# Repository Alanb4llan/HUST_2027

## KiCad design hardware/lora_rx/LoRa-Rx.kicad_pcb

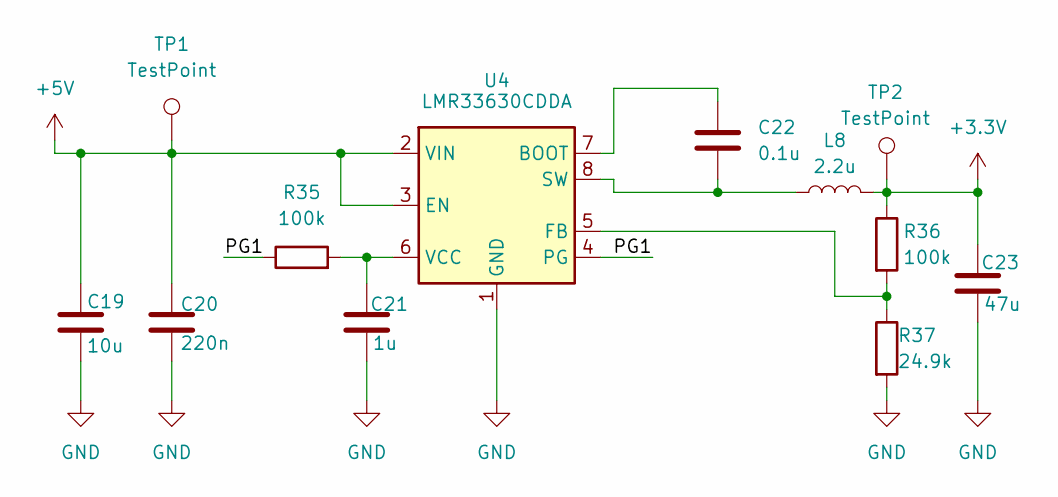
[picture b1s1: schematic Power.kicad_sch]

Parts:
C19: 10u; C_Elec_6.3x5.4
C20: 220n; C_0402_1005Metric_Pad0.74x0.62mm_HandSolder
C21: 1u; C_0402_1005Metric_Pad0.74x0.62mm_HandSolder
C22: 0.1u; C_0402_1005Metric_Pad0.74x0.62mm_HandSolder
C23: 47u; C_Elec_6.3x5.4
L8: 2.2u; L_7.3x7.3_H4.5
R35, R36: 100k; R_0402_1005Metric_Pad0.72x0.64mm_HandSolder
R37: 24.9k; R_0402_1005Metric_Pad0.72x0.64mm_HandSolder
TP1, TP2: TestPoint; TestPoint_THTPad_D1.0mm_Drill0.5mm
U4: LMR33630CDDA; Texas_HSOP-8-1EP_3.9x4.9mm_P1.27mm_ThermalVias

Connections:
+3.3V: C23.1, L8.2, R36.1, TP2.1 (1_1); also elsewhere on the board
+5V: C19.1, C20.1, TP1.1 (1_1), U4.2 (VIN), U4.3 (EN); also elsewhere on the board
/Power/PG1: R35.1, U4.4 (PG)
GND: C19.2, C20.2, C21.2, C23.2, R37.2, U4.1 (GND), U4.9 (GND); also elsewhere on the board
unnamed: C22.1, U4.7 (BOOT)
unnamed: R36.2, R37.1, U4.5 (FB)
unnamed: C22.2, L8.1, U4.8 (SW)
unnamed: C21.1, R35.2, U4.6 (VCC)

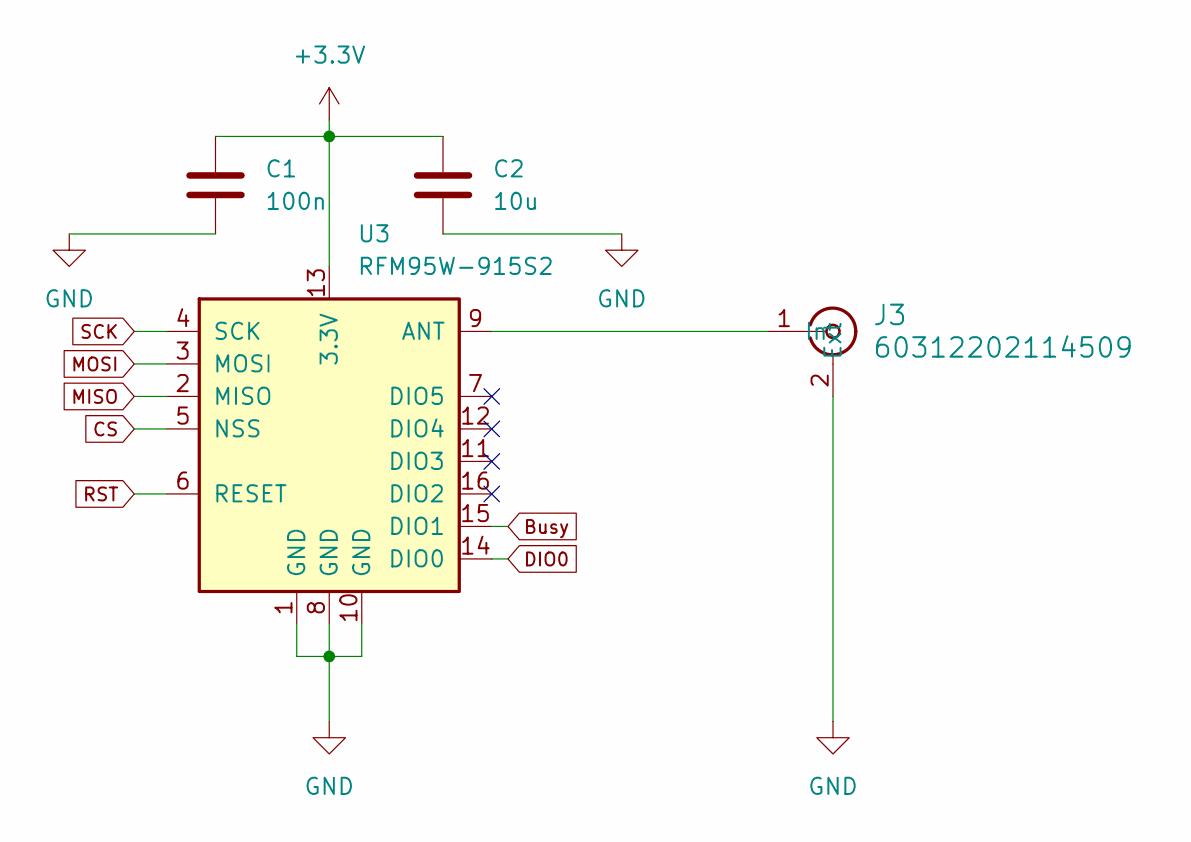
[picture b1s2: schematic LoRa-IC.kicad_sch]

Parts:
C1: 100n; C_0402_1005Metric_Pad0.74x0.62mm_HandSolder
C2: 10u; C_0603_1608Metric_Pad1.08x0.95mm_HandSolder
J3: 60312202114509; CONN_60312202114509_WRE
U3: RFM95W-915S2; HOPERF_RFM9XW_SMD

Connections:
+3.3V: C1.1, C2.1, U3.13 (3.3V); also elsewhere on the board
Busy: U3.15 (DIO1); also elsewhere on the board
CS: U3.5 (NSS); also elsewhere on the board
DIO0: U3.14 (DIO0); also elsewhere on the board
GND: C1.2, C2.2, J3.2 (Ext), J3.3 (Ext), J3.4 (Ext), J3.5 (Ext), U3.1 (GND), U3.8 (GND), U3.10 (GND); also elsewhere on the board
MISO: U3.2 (MISO); also elsewhere on the board
MOSI: U3.3 (MOSI); also elsewhere on the board
unnamed: J3.1 (In), U3.9 (ANT)
RST: U3.6 (RESET); also elsewhere on the board
SCK: U3.4 (SCK); also elsewhere on the board

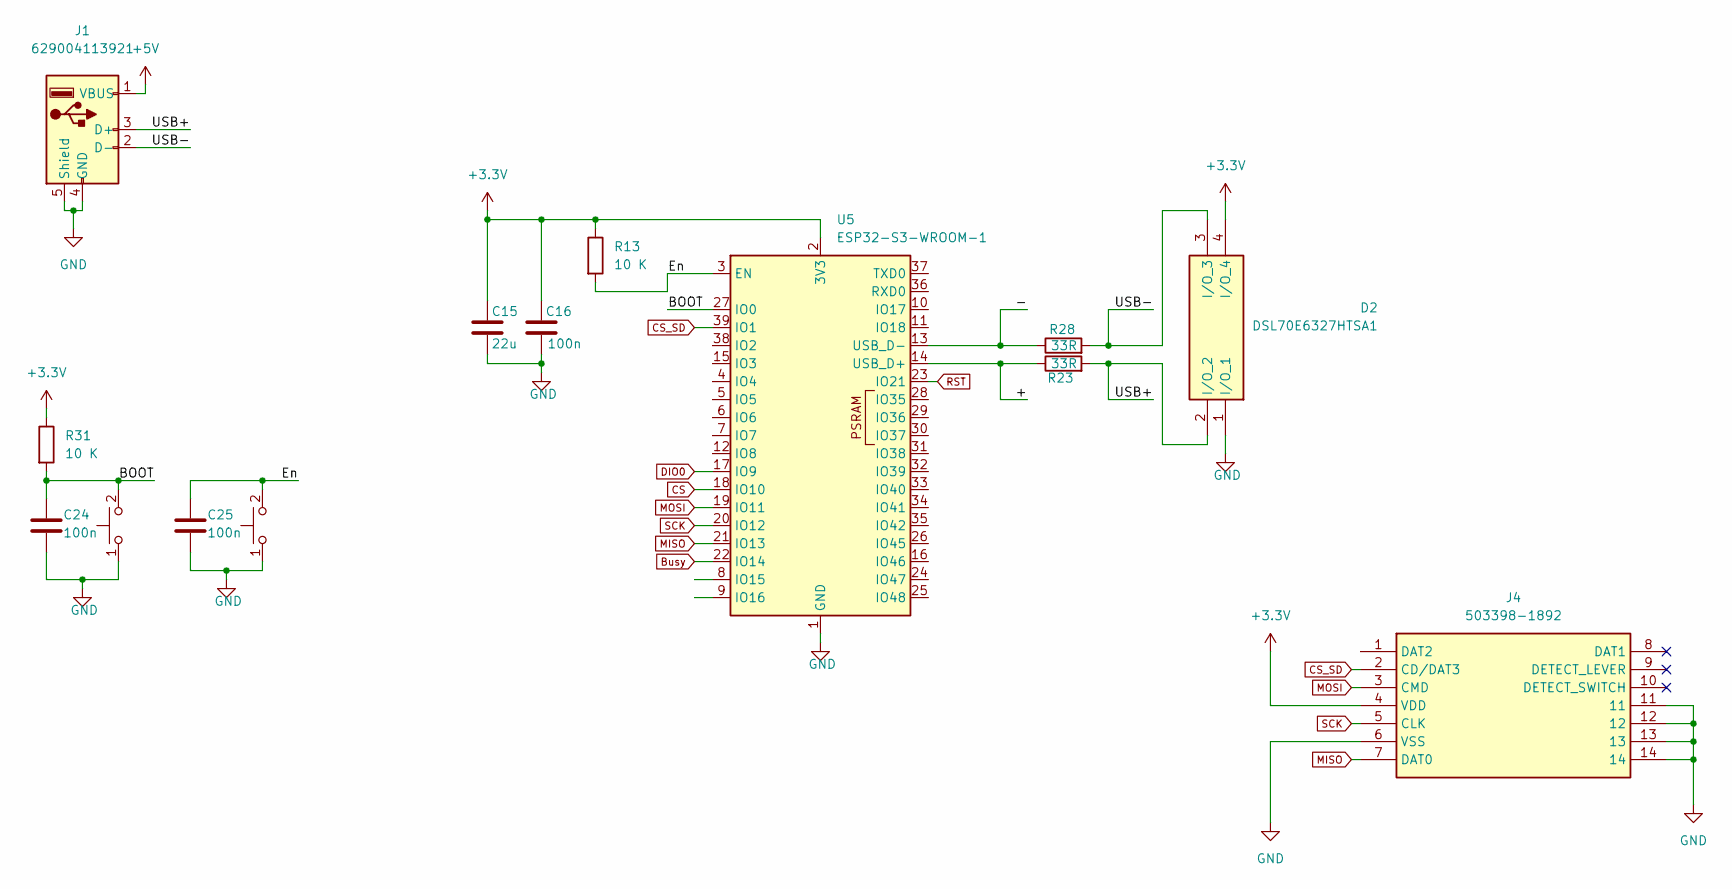
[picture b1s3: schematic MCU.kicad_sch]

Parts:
C15: 22u; C_1206_3216Metric_Pad1.33x1.80mm_HandSolder
C16, C24, C25: 100n; C_0402_1005Metric_Pad0.74x0.62mm_HandSolder
D2: DSL70E6327HTSA1; Mouser Part Number 726-DSL70E6327HTSA1
IC1, IC2: TS04-66-65-BK-260-SMT; TS046665BK260SMT; Mouser Part Number 179-TS046665BK260SMT
J1: 629004113921; Mouser Part Number 710-629004113921
J4: 503398-1892; 5033981892; Mouser Part Number 538-503398-1892
R13, R31: 10 K; R_0402_1005Metric_Pad0.72x0.64mm_HandSolder
R23, R28: 33R; R_0402_1005Metric_Pad0.72x0.64mm_HandSolder
U5: ESP32-S3-WROOM-1; ESP32-S3-WROOM-1U

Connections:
+3.3V: C15.1, C16.1, D2.4 (I/O_4), J4.4 (VDD), R13.1, R31.1, U5.2 (3V3); also elsewhere on the board
+5V: J1.1 (VBUS); also elsewhere on the board
/MCU/+: R23.1, U5.14 (USB_D+)
/MCU/-: R28.1, U5.13 (USB_D-)
/MCU/BOOT: C24.1, IC1.2, IC1.4, R31.2, U5.27 (IO0)
/MCU/En: C25.1, IC2.2, IC2.4, R13.2, U5.3 (EN)
/MCU/USB+: D2.2 (I/O_2), J1.3 (D+), R23.2
/MCU/USB-: D2.3 (I/O_3), J1.2 (D-), R28.2
Busy: U5.22 (IO14); also elsewhere on the board
CS: U5.18 (IO10); also elsewhere on the board
CS_SD: J4.2 (CD/DAT3), U5.39 (IO1)
DIO0: U5.17 (IO9); also elsewhere on the board
GND: C15.2, C16.2, C24.2, C25.2, D2.1 (I/O_1), IC1.1, IC1.3, IC2.1, IC2.3, J1.4 (GND), J1.5 (Shield), J1.6 (Shield), J4.6 (VSS), J4.11, J4.12, J4.13, J4.14, U5.1 (GND), U5.40 (GND), U5.41 (GND); also elsewhere on the board
MISO: J4.7 (DAT0), U5.21 (IO13); also elsewhere on the board
MOSI: J4.3 (CMD), U5.19 (IO11); also elsewhere on the board
RST: U5.23 (IO21); also elsewhere on the board
SCK: J4.5 (CLK), U5.20 (IO12); also elsewhere on the board

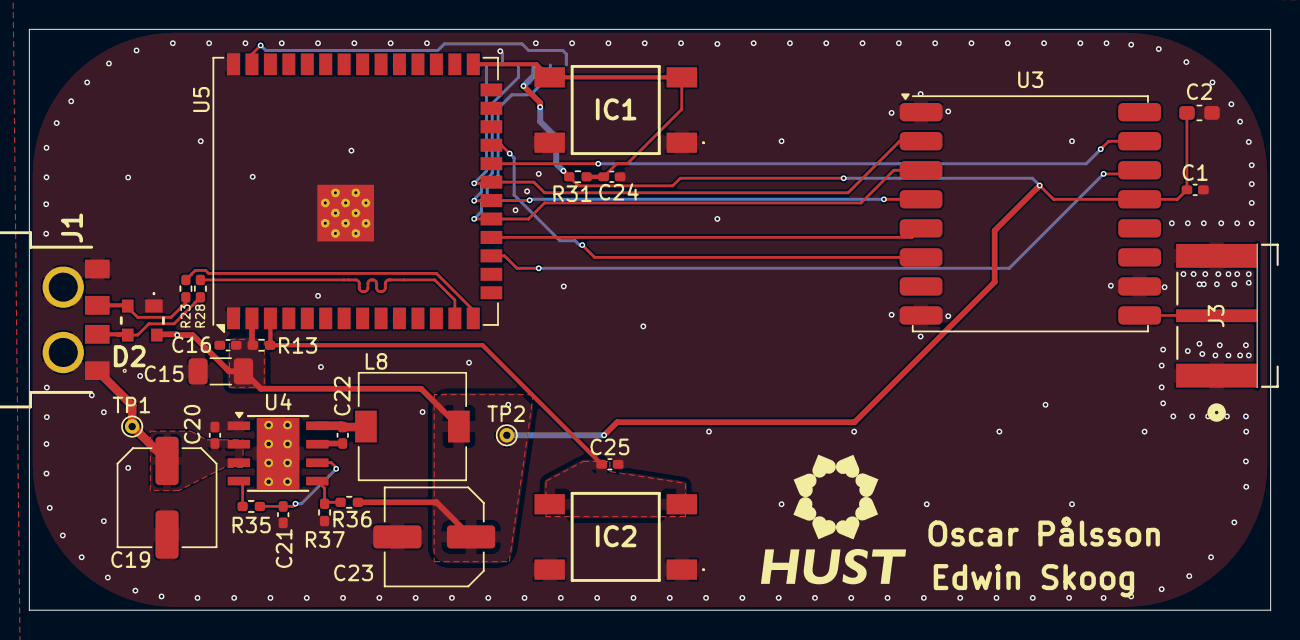
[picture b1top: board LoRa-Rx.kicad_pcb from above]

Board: 2 copper layers, 85.5 x 40.0 mm, 30 parts (1 on the bottom side), 23 nets.

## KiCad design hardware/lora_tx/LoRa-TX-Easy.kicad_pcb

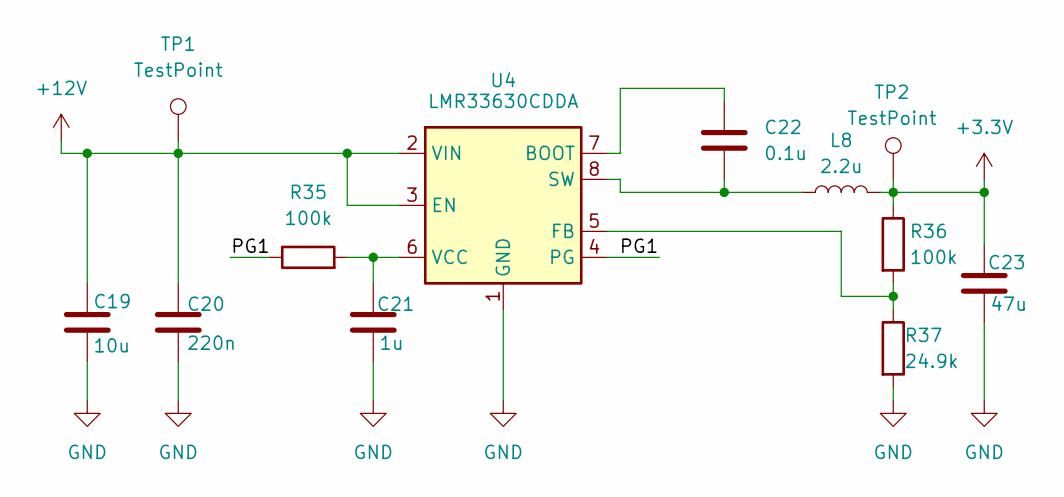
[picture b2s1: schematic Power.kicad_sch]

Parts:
C19: 10u; C_Elec_6.3x5.4
C20: 220n; C_0402_1005Metric_Pad0.74x0.62mm_HandSolder
C21: 1u; C_0402_1005Metric_Pad0.74x0.62mm_HandSolder
C22: 0.1u; C_0402_1005Metric_Pad0.74x0.62mm_HandSolder
C23: 47u; C_Elec_6.3x5.4
L8: 2.2u; L_7.3x7.3_H4.5
R35, R36: 100k; R_0402_1005Metric_Pad0.72x0.64mm_HandSolder
R37: 24.9k; R_0402_1005Metric_Pad0.72x0.64mm_HandSolder
TP1, TP2: TestPoint; TestPoint_THTPad_D1.0mm_Drill0.5mm
U4: LMR33630CDDA; Texas_HSOP-8-1EP_3.9x4.9mm_P1.27mm_ThermalVias

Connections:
+3.3V: C23.1, L8.2, R36.1, TP2.1 (1_1); also elsewhere on the board
+12V: C19.1, C20.1, TP1.1 (1_1), U4.2 (VIN), U4.3 (EN); also elsewhere on the board
/Power/PG1: R35.1, U4.4 (PG)
GND: C19.2, C20.2, C21.2, C23.2, R37.2, U4.1 (GND), U4.9 (GND); also elsewhere on the board
unnamed: C22.1, U4.7 (BOOT)
unnamed: R36.2, R37.1, U4.5 (FB)
unnamed: C22.2, L8.1, U4.8 (SW)
unnamed: C21.1, R35.2, U4.6 (VCC)

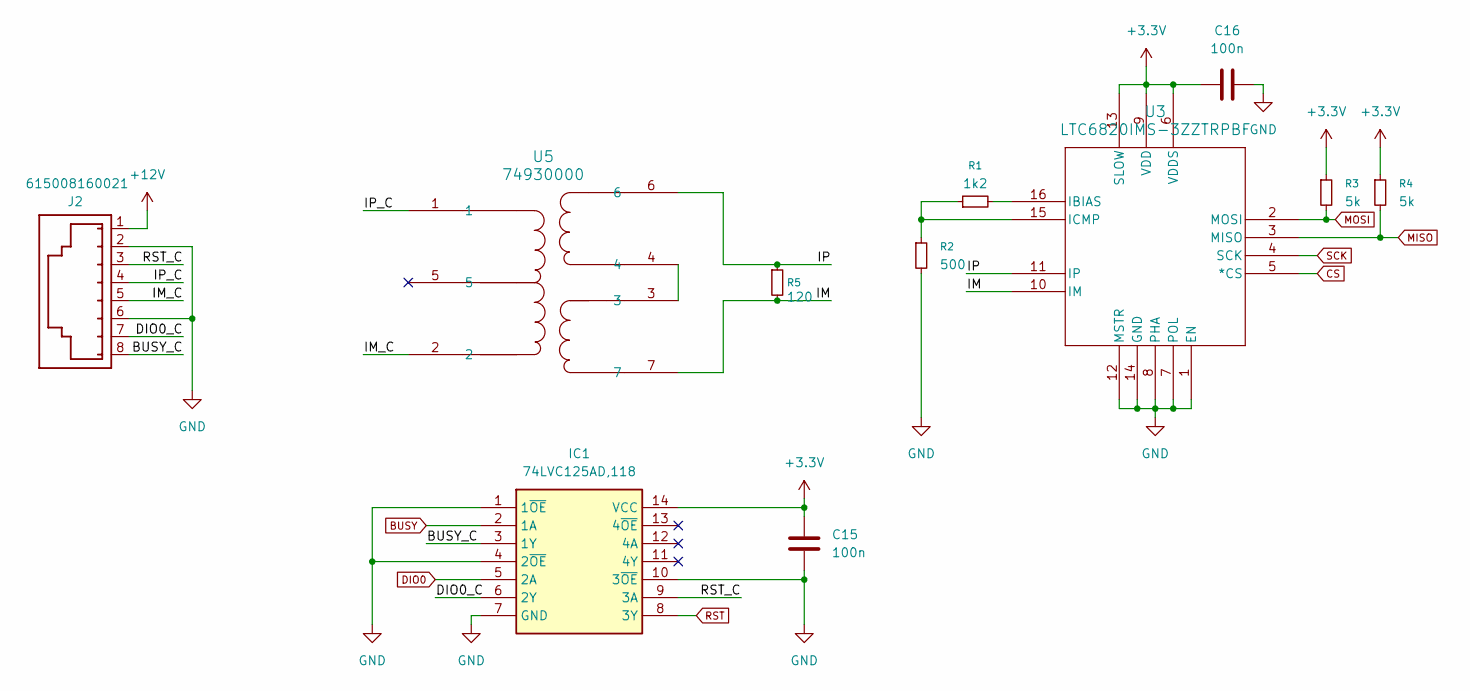
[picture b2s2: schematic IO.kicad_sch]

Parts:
C15, C16: 100n; C_0402_1005Metric_Pad0.74x0.62mm_HandSolder
IC1: 74LVC125AD,118; 74LVC125AD118; Mouser Part Number 771-74LVC125AD-T
J2: 615008160021; J_Wurth_WR-MJ_615008160021
R1: 1k2; R_0402_1005Metric_Pad0.72x0.64mm_HandSolder
R2: 500; R_0402_1005Metric_Pad0.72x0.64mm_HandSolder
R3, R4: 5k; R_0402_1005Metric_Pad0.72x0.64mm_HandSolder
R5: 120; R_0402_1005Metric_Pad0.72x0.64mm_HandSolder
U3: LTC6820IMS-3ZZTRPBF; MS_05-08-1669_ADI
U5: 74930000; SON_930000_WRE

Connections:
+3.3V: C15.1, C16.1, IC1.14 (VCC), R3.1, R4.1, U3.6 (VDDS), U3.9 (VDD), U3.13 (SLOW); also elsewhere on the board
+12V: J2.1; also elsewhere on the board
/IO/BUSY_C: IC1.3 (1Y), J2.8
/IO/DIO0_C: IC1.6 (2Y), J2.7
/IO/IM: R5.2, U3.10 (IM), U5.7
/IO/IM_C: J2.5, U5.2
/IO/IP: R5.1, U3.11 (IP), U5.6
/IO/IP_C: J2.4, U5.1
/IO/RST_C: IC1.9 (3A), J2.3
BUSY: IC1.2 (1A); also elsewhere on the board
CS: U3.5 (*CS); also elsewhere on the board
DIO0: IC1.5 (2A); also elsewhere on the board
GND: C15.2, C16.2, IC1.1 (1~OE), IC1.4 (2~OE), IC1.7 (GND), IC1.10 (3~OE), J2.2, J2.6, R2.2, U3.1 (EN), U3.7 (POL), U3.8 (PHA), U3.12 (MSTR), U3.14 (GND); also elsewhere on the board
MISO: R4.2, U3.3 (MISO); also elsewhere on the board
MOSI: R3.2, U3.2 (MOSI); also elsewhere on the board
unnamed: R1.2, U3.16 (IBIAS)
unnamed: R1.1, R2.1, U3.15 (ICMP)
unnamed: U5.3, U5.4
RST: IC1.8 (3Y); also elsewhere on the board
SCK: U3.4 (SCK); also elsewhere on the board

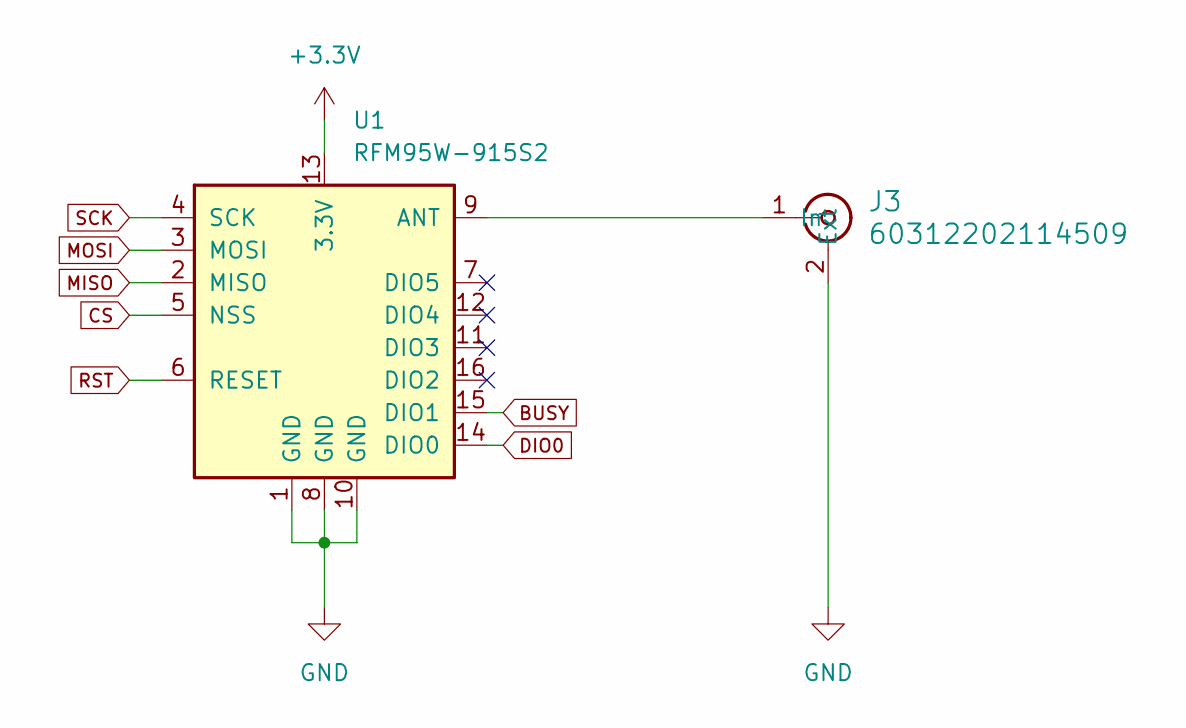
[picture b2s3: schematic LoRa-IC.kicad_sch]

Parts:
J3: 60312202114509; CONN_60312202114509_WRE
U1: RFM95W-915S2; HOPERF_RFM9XW_SMD

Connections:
+3.3V: U1.13 (3.3V); also elsewhere on the board
BUSY: U1.15 (DIO1); also elsewhere on the board
CS: U1.5 (NSS); also elsewhere on the board
DIO0: U1.14 (DIO0); also elsewhere on the board
GND: J3.2 (Ext), J3.3 (Ext), J3.4 (Ext), J3.5 (Ext), U1.1 (GND), U1.8 (GND), U1.10 (GND); also elsewhere on the board
MISO: U1.2 (MISO); also elsewhere on the board
MOSI: U1.3 (MOSI); also elsewhere on the board
unnamed: J3.1 (In), U1.9 (ANT)
RST: U1.6 (RESET); also elsewhere on the board
SCK: U1.4 (SCK); also elsewhere on the board

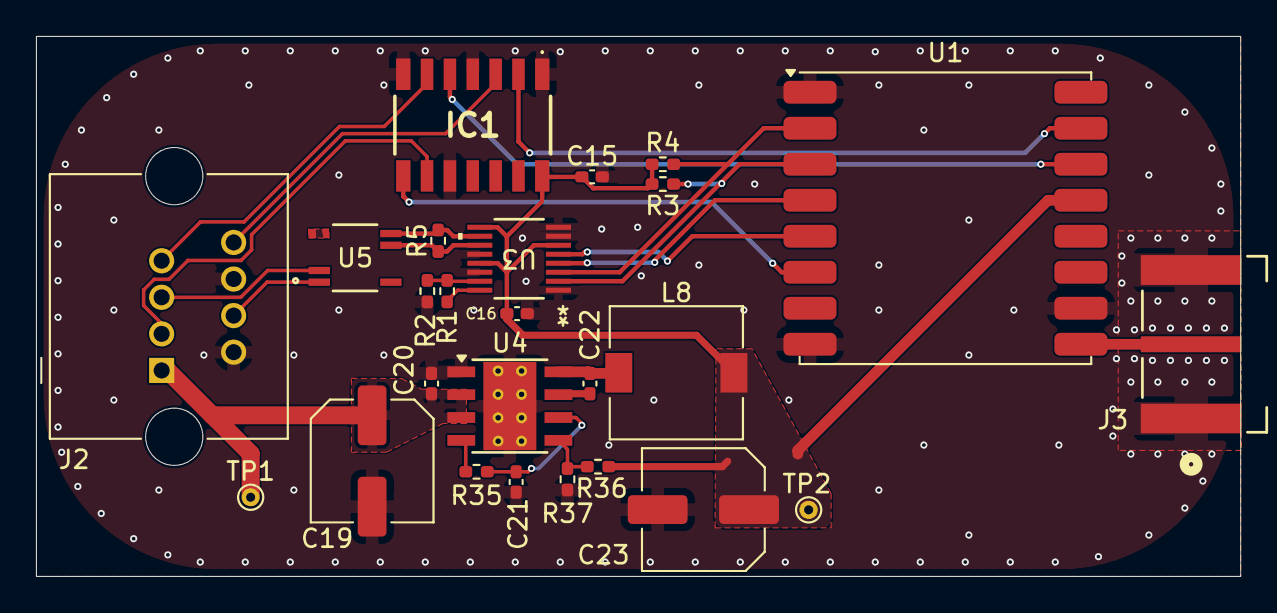
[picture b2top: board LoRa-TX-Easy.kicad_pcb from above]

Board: 2 copper layers, 66.9 x 30.0 mm, 25 parts (0 on the bottom side), 26 nets.

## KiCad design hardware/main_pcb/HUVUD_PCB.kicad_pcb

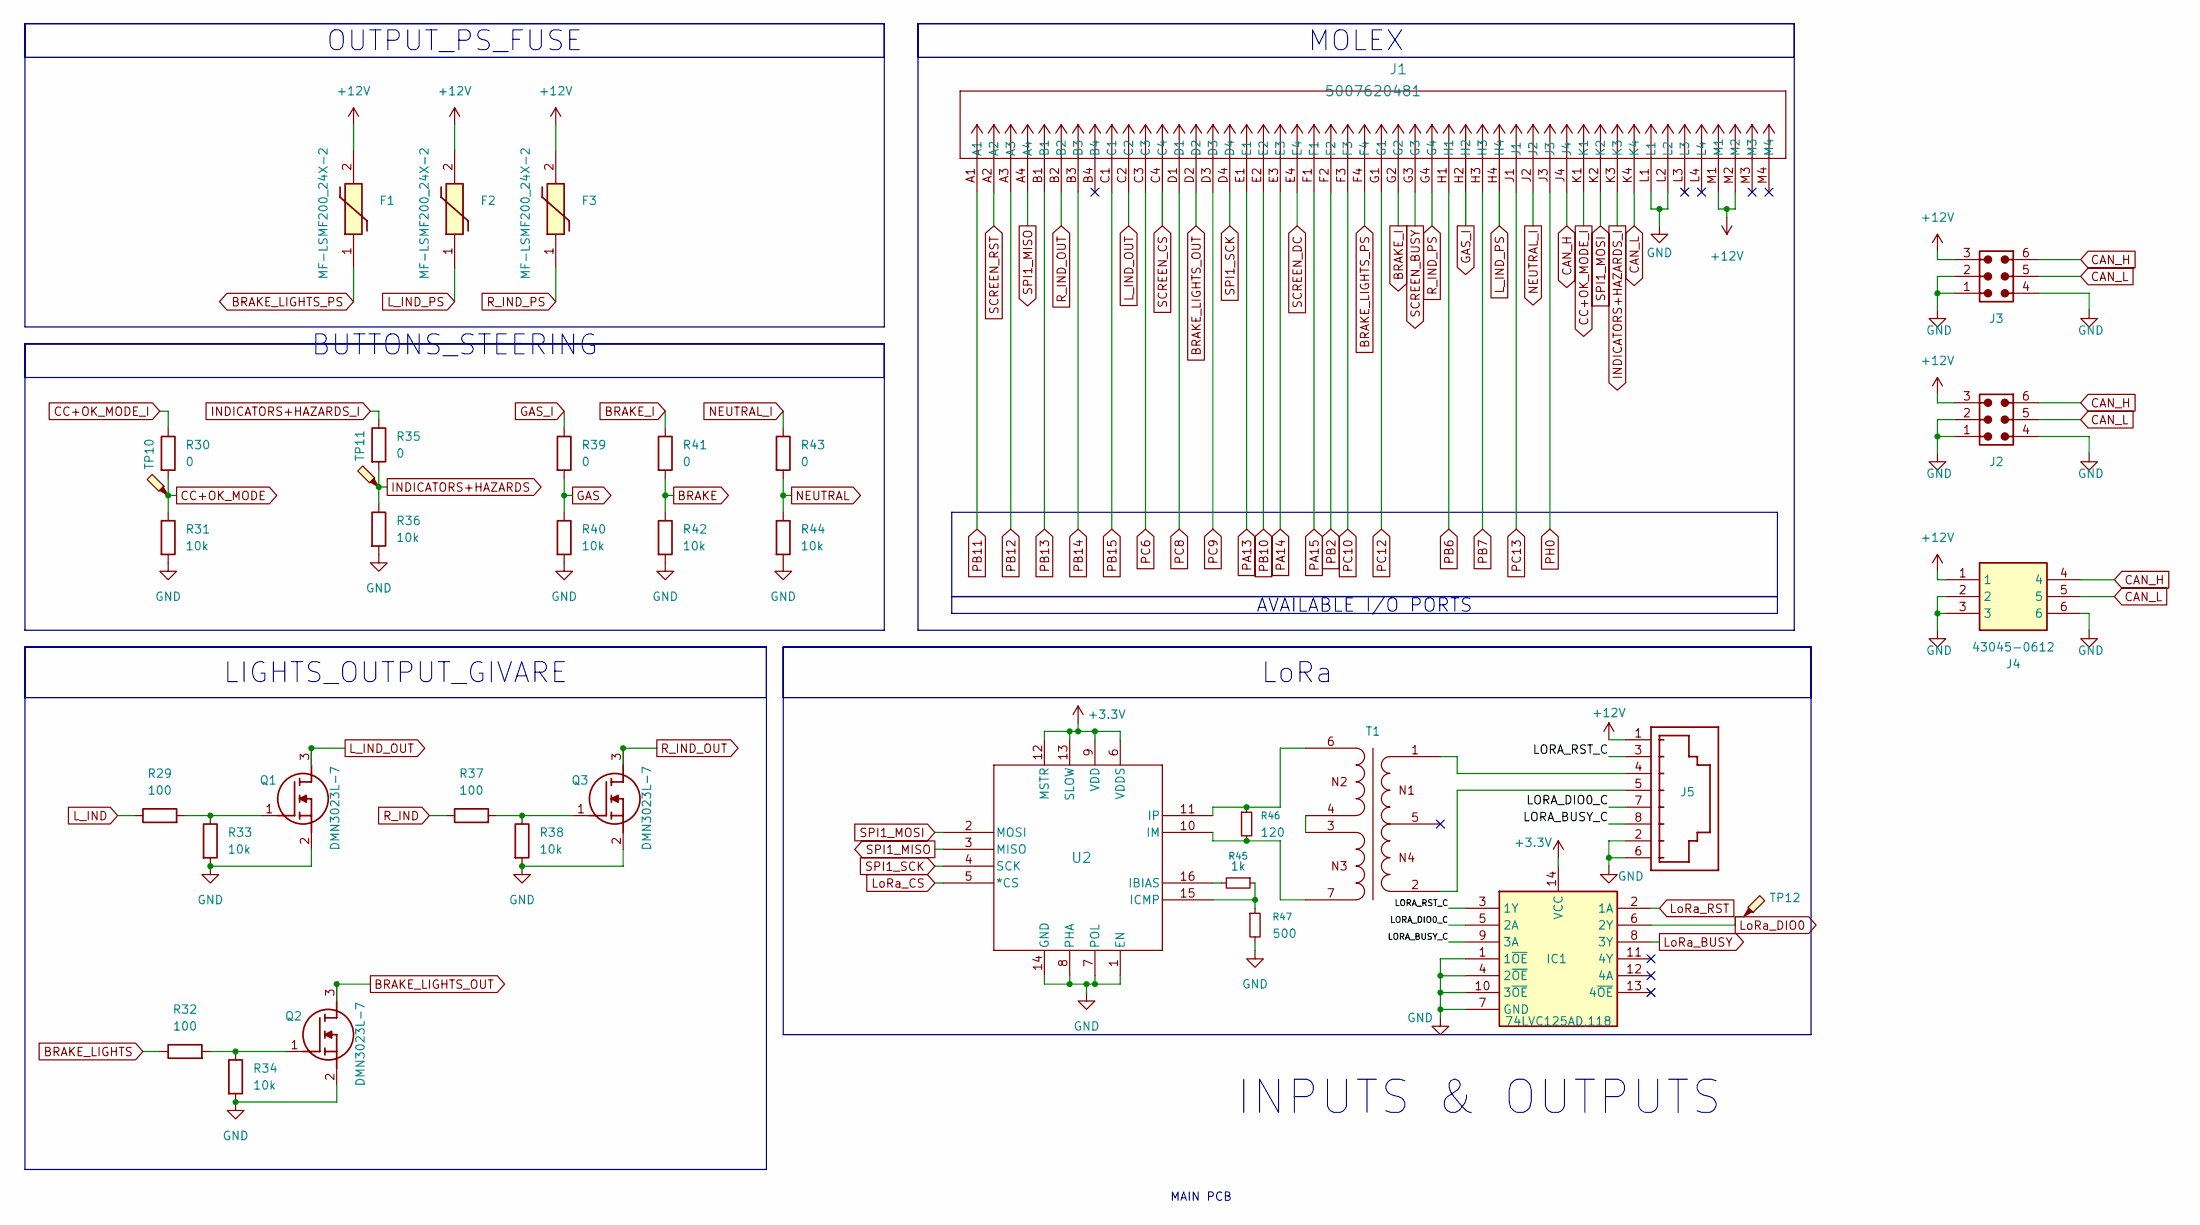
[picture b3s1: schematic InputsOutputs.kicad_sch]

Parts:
F1, F2, F3: MF-LSMF200_24X-2; FUSC7451X160N; Mouser Part Number 652-MF-LSMF200/24X-2
IC1: 74LVC125AD,118; 74LVC125AD118; Mouser Part Number 771-74LVC125AD-T
J1: 5007620481; CONN_SD-500762-001_MOL
J2, J3: 66200621122; J_Wurth_WR-MPC3_66200621122; Working Voltage (V (AC)) 250
J4: 43045-0612; 43045-06YY_121314; Mouser Part Number 538-43045-0612
J5: 615008160021
Q1, Q2, Q3: DMN3023L-7; SOT96P240X110-3N; Mouser Part Number 621-DMN3023L-7
R29, R32, R37: 100; R_Wurth_WRIS-RSKS-0603_W
R30, R35, R39, R41, R43: 0; R_Wurth_WRIS-RSKS-0603_W
R31, R33, R34, R36, R38, R40, R42, R44: 10k; R_Wurth_WRIS-RSKS-0603_W
R45: 1k; R_Wurth_WRIS-RSKS-0603_W
R46: 120; R_Wurth_WRIS-RSKS-0603_W
R47: 500; R_Wurth_WRIS-RSKS-0603_W
T1: 4532_74930000; T_Wurth_WE-STST-4532_74930000; Part Number 74930000
TP10, TP11, TP12: TestPoint_Probe; TestPoint_THTPad_2.0x2.0mm_Drill1.0mm
U2: LTC6820IMS-3ZZTRPBF; MS_05-08-1669_ADI-M

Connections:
+3.3V: IC1.14 (VCC), U2.6 (VDDS), U2.9 (VDD), U2.12 (MSTR), U2.13 (SLOW); also elsewhere on the board
+12V: F1.2, F2.2, F3.2, J1.M1, J1.M2, J2.3, J3.3, J4.1, J5.1; also elsewhere on the board
/Outputs/LORA_BUSY_C: IC1.9 (3A), J5.8
/Outputs/LORA_DIO0_C: IC1.5 (2A), J5.7
/Outputs/LORA_RST_C: IC1.3 (1Y), J5.3
BRAKE: R41.2, R42.1; also elsewhere on the board
BRAKE_I: J1.G2, R41.1
BRAKE_LIGHTS: R32.1; also elsewhere on the board
BRAKE_LIGHTS_OUT: J1.D2, Q2.3 (D)
BRAKE_LIGHTS_PS: F1.1, J1.F4
CAN_H: J1.J4, J2.6, J3.6, J4.4; also elsewhere on the board
CAN_L: J1.K4, J2.5, J3.5, J4.5; also elsewhere on the board
CC+OK_MODE: R30.2, R31.1, TP10.1; also elsewhere on the board
CC+OK_MODE_I: J1.K1, R30.1
GAS: R39.2, R40.1; also elsewhere on the board
GAS_I: J1.H2, R39.1
GND: IC1.1 (1~OE), IC1.4 (2~OE), IC1.7 (GND), IC1.10 (3~OE), J1.L1, J1.L2, J2.1, J2.2, J2.4, J3.1, J3.2, J3.4, J4.2, J4.3, J4.6, J5.2, J5.6, Q1.2 (S), Q2.2 (S), Q3.2 (S), R31.2, R33.2, R34.2, R36.2, R38.2, R40.2, R42.2, R44.2, R47.2, U2.1 (EN), U2.7 (POL), U2.8 (PHA), U2.14 (GND); also elsewhere on the board
INDICATORS+HAZARDS: R35.2, R36.1, TP11.1; also elsewhere on the board
INDICATORS+HAZARDS_I: J1.K3, R35.1
L_IND: R29.1; also elsewhere on the board
L_IND_OUT: J1.C2, Q1.3 (D)
L_IND_PS: F2.1, J1.H4
LoRa_BUSY: IC1.8 (3Y); also elsewhere on the board
LoRa_CS: U2.5 (*CS); also elsewhere on the board
LoRa_DIO0: IC1.6 (2Y), TP12.1; also elsewhere on the board
LoRa_RST: IC1.2 (1A); also elsewhere on the board
NEUTRAL: R43.2, R44.1; also elsewhere on the board
NEUTRAL_I: J1.J2, R43.1
unnamed: J5.4, T1.1
unnamed: J5.5, T1.2
unnamed: Q1.1 (G), R29.2, R33.1
unnamed: Q2.1 (G), R32.2, R34.1
unnamed: Q3.1 (G), R37.2, R38.1
unnamed: T1.3, T1.4
unnamed: R45.2, U2.16 (IBIAS)
unnamed: R45.1, R47.1, U2.15 (ICMP)
unnamed: R46.2, T1.7, U2.10 (IM)
unnamed: R46.1, T1.6, U2.11 (IP)
PA13: J1.E1; also elsewhere on the board
PA14: J1.E3; also elsewhere on the board
PA15: J1.F1; also elsewhere on the board
PB2: J1.F2; also elsewhere on the board
PB6: J1.H1; also elsewhere on the board
PB7: J1.H3; also elsewhere on the board
PB10: J1.E2; also elsewhere on the board
PB11: J1.A1; also elsewhere on the board
PB12: J1.A3; also elsewhere on the board
PB13: J1.B1; also elsewhere on the board
PB14: J1.B3; also elsewhere on the board
PB15: J1.C1; also elsewhere on the board
PC6: J1.C3
PC8: J1.D1; also elsewhere on the board
PC9: J1.D3; also elsewhere on the board
PC10: J1.F3; also elsewhere on the board
PC12: J1.G1; also elsewhere on the board
PC13: J1.J1; also elsewhere on the board
PH0: J1.J3; also elsewhere on the board
R_IND: R37.1; also elsewhere on the board
R_IND_OUT: J1.B2, Q3.3 (D)
R_IND_PS: F3.1, J1.G4
SCREEN_BUSY: J1.G3; also elsewhere on the board
SCREEN_CS: J1.C4; also elsewhere on the board
SCREEN_DC: J1.E4; also elsewhere on the board
SCREEN_RST: J1.A2; also elsewhere on the board
SPI1_MISO: J1.A4, U2.3 (MISO); also elsewhere on the board
SPI1_MOSI: J1.K2, U2.2 (MOSI); also elsewhere on the board
SPI1_SCK: J1.D4, U2.4 (SCK); also elsewhere on the board

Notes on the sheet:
MAIN PCB
INPUTS & OUTPUTS
AVAILABLE I/O PORTS
OUTPUT_PS_FUSE
LIGHTS_OUTPUT_GIVARE
LoRa
MOLEX
BUTTONS_STEERING

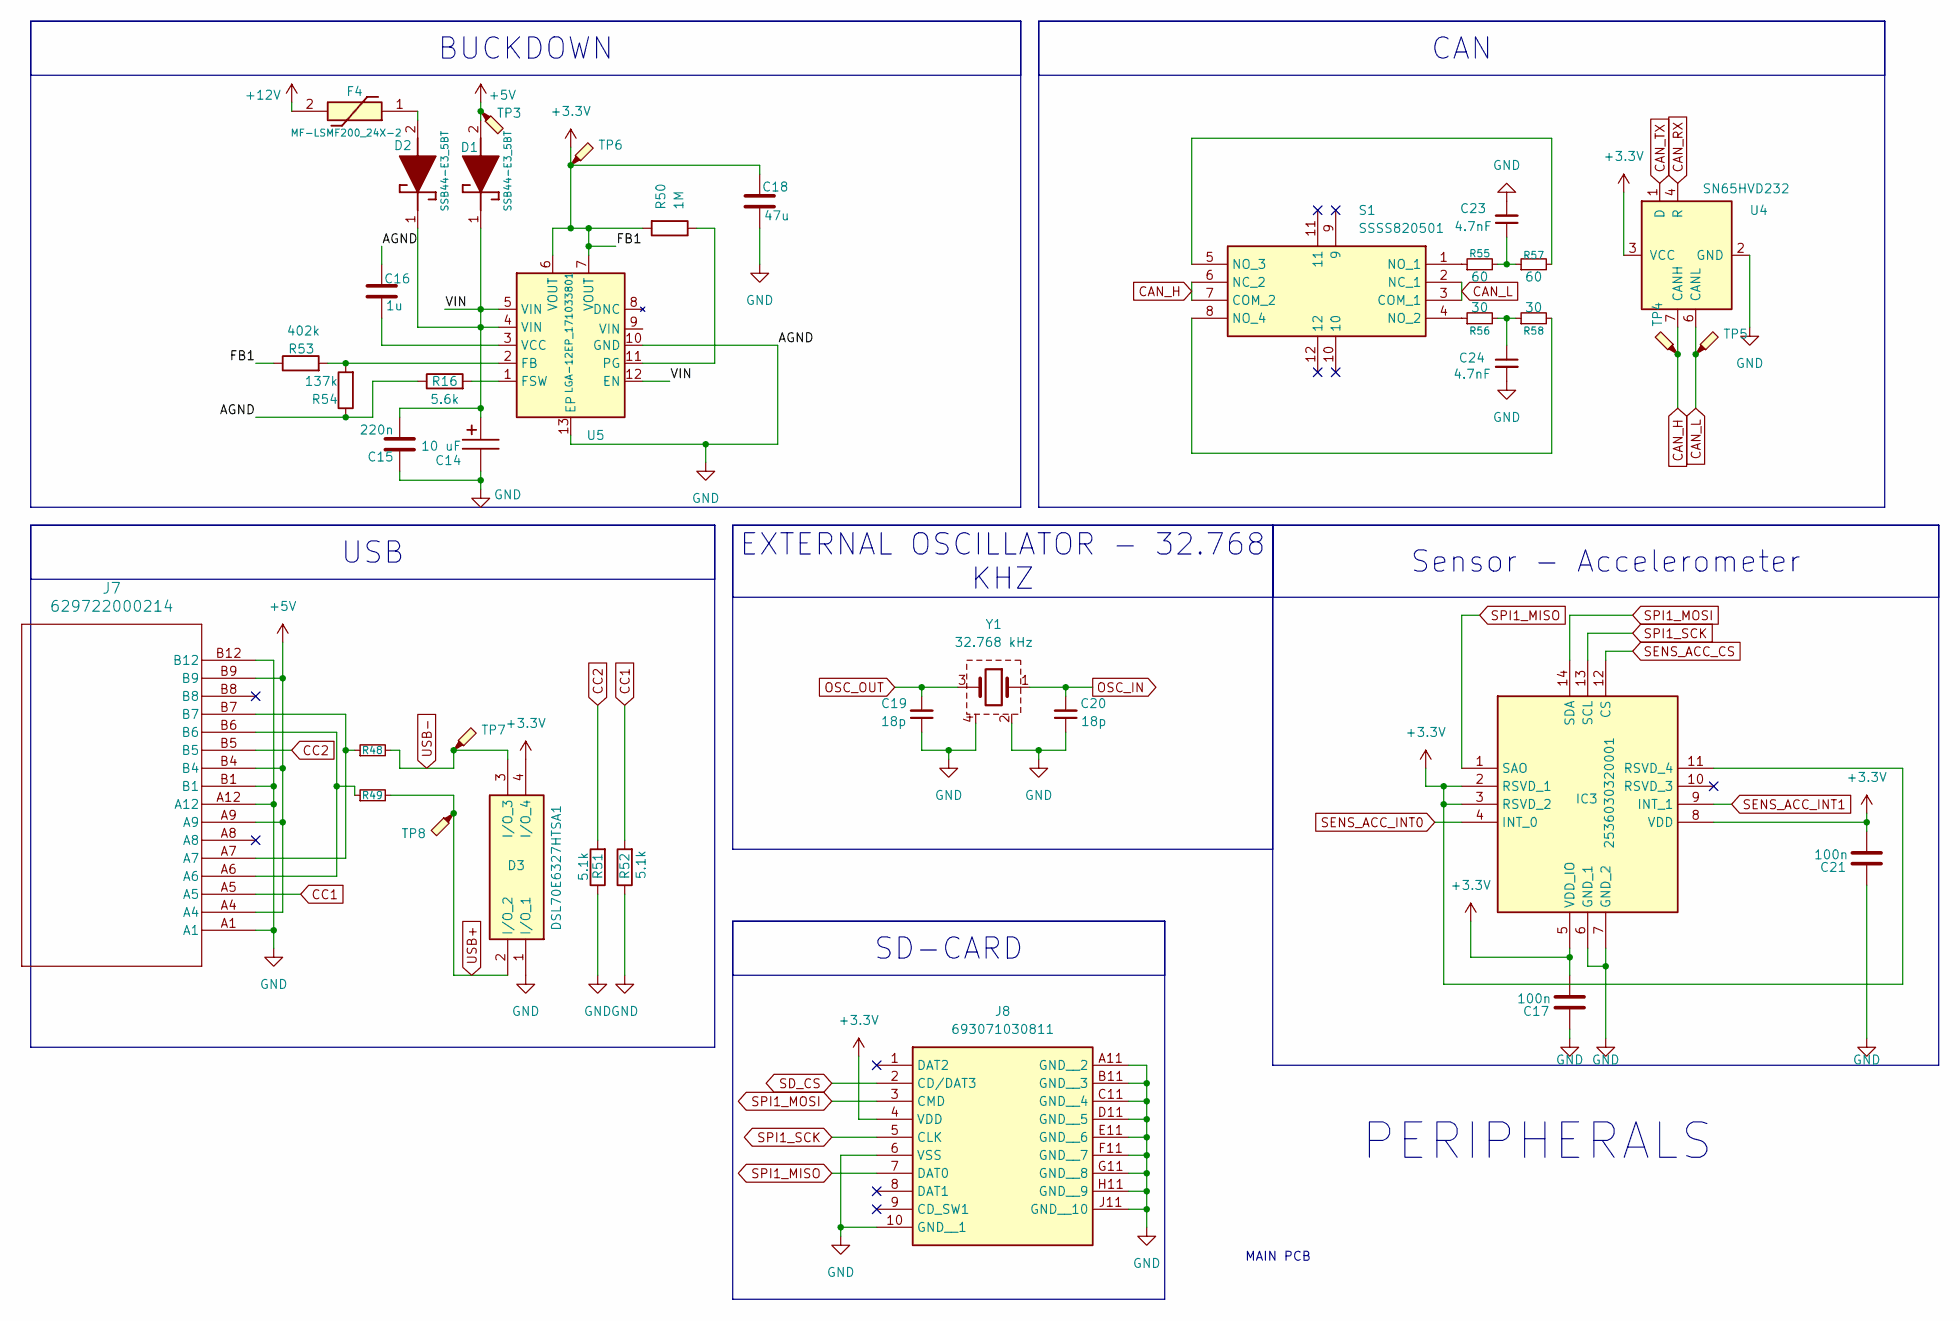
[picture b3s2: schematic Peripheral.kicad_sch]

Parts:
C14: 10 uF; C_0603_1608Metric_Pad1.08x0.95mm_HandSolder; Voltage 16.0; Part Number 865080340001
C15: 220n; C_0603_1608Metric_Pad1.08x0.95mm_HandSolder
C16: 1u; C_0603_1608Metric_Pad1.08x0.95mm_HandSolder
C17, C21: 100n; C_0603_1608Metric_Pad1.08x0.95mm_HandSolder
C18: 47u; CP_Radial_D8.0mm_P5.00mm
C19, C20: 18p; C_0603_1608Metric_Pad1.08x0.95mm_HandSolder
C23, C24: 4.7nF; C_0603_1608Metric_Pad1.08x0.95mm_HandSolder
D1, D2: SSB44-E3_5BT; DIOM5436X244N; Mouser Part Number 625-SSB44-E3/5BT
D3: DSL70E6327HTSA1; Mouser Part Number 726-DSL70E6327HTSA1
F4: MF-LSMF200_24X-2; FUSC7451X160N; Mouser Part Number 652-MF-LSMF200/24X-2
IC3: 2536030320001; Manufacturer_Part_Number 2536030320001
J7: 629722000214; J_Wurth_WR-USB_629722000214
J8: 693071030811; Mouser Part Number 710-693071030811
R16: 5.6k
R48, R49: 33; R_Wurth_WRIS-RSKS-0603_W
R50: 1M; R_Wurth_WRIS-RSKS-0603_W
R51, R52: 5.1k; R_Wurth_WRIS-RSKS-0603_W
R53: 402k; R_Wurth_WRIS-RSKS-0603_W
R54: 137k; R_Wurth_WRIS-RSKS-0603_W
R55, R57: 60; R_Wurth_WRIS-RSKS-0603_W
R56, R58: 30; R_Wurth_WRIS-RSKS-0603_W
S1: SSSS820501; Mouser Part Number 688-SSSS820501
TP3: TestPoint_Probe
TP4, TP5, TP6, TP7, TP8: TestPoint_Probe; TestPoint_THTPad_2.0x2.0mm_Drill1.0mm
U4: SN65HVD232; SOIC127P600X175-8N
U5: LGA-12EP_171033801; U_Wurth_WPME-VDLM-LGA-12EP
Y1: 32.768 kHz; Y_Wurth_WE-XTAL_Watch-85SMX; Part Number 830003000

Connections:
+3.3V: C17.2, C18.1, C21.2, D3.4 (I/O), IC3.2 (RSVD_1), IC3.3 (RSVD_2), IC3.5 (VDD_IO), IC3.8 (VDD), IC3.11 (RSVD_4), J8.4 (VDD), R50.2, R53.1, TP6.1, U4.3 (VCC), U5.6 (VOUT), U5.7 (VOUT); also elsewhere on the board
+5V: D1.2 (A), J7.A4, J7.A9, J7.B4, J7.B9, TP3.1
+12V: F4.2; also elsewhere on the board
/Peripheral/VIN: C14.1, C15.2, D1.1 (K), D2.1 (K), U5.4 (VIN), U5.5 (VIN), U5.12 (EN)
CAN_H: S1.6 (NC_2), S1.7 (COM_2), TP4.1, U4.7 (CANH); also elsewhere on the board
CAN_L: S1.2 (NC_1), S1.3 (COM_1), TP5.1, U4.6 (CANL); also elsewhere on the board
CAN_RX: U4.4 (R); also elsewhere on the board
CAN_TX: U4.1 (D); also elsewhere on the board
CC1: J7.A5, R52.2
CC2: J7.B5, R51.2
GND: C14.2, C15.1, C16.1, C17.1, C18.2, C19.1, C20.1, C21.1, C23.2, C24.2, D3.1 (I/O), IC3.6 (GND_1), IC3.7 (GND_2), J7.A1, J7.A12, J7.B1, J7.B12, J8.6 (VSS), J8.10 (GND__1), J8.A11 (GND__2), J8.B11 (GND__3), J8.C11 (GND__4), J8.D11 (GND__5), J8.E11 (GND__6), J8.F11 (GND__7), J8.G11 (GND__8), J8.H11 (GND__9), J8.J11 (GND__10), R16.1, R51.1, R52.1, R54.1, U4.2 (GND), U5.10 (GND), U5.13 (EP), Y1.2 (GND), Y1.4 (GND1); also elsewhere on the board
unnamed: C23.1, R55.2, R57.1
unnamed: C24.1, R56.2, R58.1
unnamed: D2.2 (A), F4.1
unnamed: J7.A6, J7.B6, R49.1
unnamed: J7.A7, J7.B7, R48.1
unnamed: R55.1, S1.1 (NO_1)
unnamed: R56.1, S1.4 (NO_2)
unnamed: R57.2, S1.5 (NO_3)
unnamed: R58.2, S1.8 (NO_4)
unnamed: R53.2, R54.2, U5.2 (FB)
unnamed: R16.2, U5.1 (FSW)
unnamed: R50.1, U5.11 (PG)
unnamed: C16.2, U5.3 (VCC)
OSC_IN: C20.2, Y1.1; also elsewhere on the board
OSC_OUT: C19.2, Y1.3; also elsewhere on the board
SD_CS: J8.2 (CD/DAT3); also elsewhere on the board
SENS_ACC_CS: IC3.12 (CS); also elsewhere on the board
SENS_ACC_INT0: IC3.4 (INT_0); also elsewhere on the board
SENS_ACC_INT1: IC3.9 (INT_1); also elsewhere on the board
SPI1_MISO: IC3.1 (SAO), J8.7 (DAT0); also elsewhere on the board
SPI1_MOSI: IC3.14 (SDA), J8.3 (CMD); also elsewhere on the board
SPI1_SCK: IC3.13 (SCL), J8.5 (CLK); also elsewhere on the board
USB+: D3.2 (I/O), R49.2, TP8.1; also elsewhere on the board
USB-: D3.3 (I/O), R48.2, TP7.1; also elsewhere on the board

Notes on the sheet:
MAIN PCB
PERIPHERALS
BUCKDOWN
USB
CAN
Sensor - Accelerometer
SD-CARD
EXTERNAL OSCILLATOR - 32.768 KHZ
